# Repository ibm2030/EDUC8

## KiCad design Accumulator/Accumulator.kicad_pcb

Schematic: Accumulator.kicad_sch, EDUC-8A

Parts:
C1, C2, C3, C4: 47nF; C_Rect_L11.0mm_W2.8mm_P10.00mm_MKT
H1, H2: Card_handle
J1, J2: 16-way-pcb-edge-Educ-8-connectors; PCB_16pin
R1: 820; R_Axial_DIN0207_L6.3mm_D2.5mm_P10.16mm_Horizontal
R2, R3, R4: 2K2; R_Axial_DIN0207_L6.3mm_D2.5mm_P10.16mm_Horizontal
U1, U3: 74LS95; DIP-14_W7.62mm_LongPads
U2, U4: 74LS05; DIP-14_W7.62mm_LongPads
U5, U10: 74LS01; DIP-14_W7.62mm_LongPads
U6: 74LS04; DIP-14_W7.62mm_LongPads
U7, U9: 7400
U8: 74LS10

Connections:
+5V: C1.1, C2.1, C3.1, C4.1, J1.2, J1.3, R1.2, R2.1, R3.1, R4.1, U1.14 (VCC), U2.14 (VCC), U3.14 (VCC), U4.14 (VCC), U5.14 (VCC), U6.14 (VCC), U7.14 (VCC), U8.14 (VCC), U9.14 (VCC), U10.14 (VCC)
A-BUS: J1.4, U5.4, U6.9
AC0: J1.11, J2.9, U1.4 (P2), U1.10 (Q3), U2.9, U9.2, U9.13, U10.3, U10.5, U10.12
AC1: J2.10, U1.3 (P1), U1.11 (Q2), U2.11
AC2: J2.11, U1.2 (P0), U1.12 (Q1), U2.13
AC3: J2.12, U1.13 (Q0), U2.1, U3.5 (P3)
AC4: J2.13, U1.1 (Ds), U3.4 (P2), U3.10 (Q3), U4.9
AC5: J2.14, U3.3 (P1), U3.11 (Q2), U4.11
AC6: J2.15, U3.2 (P0), U3.12 (Q1), U4.13
AC7: J2.16, U1.5 (P3), U2.5, U3.13 (Q0)
AC=0: J1.15, R1.1, U2.2, U2.6, U2.8, U2.10, U2.12, U4.8, U4.10, U4.12
B-BUS: J1.5, U5.1, U10.1, U10.4
C-BUS: J1.6, U10.13
CPA: U1.9 (Cp1.Rshift), U3.9 (Cp1.Rshift), U7.8
D-BUS: J1.7, U9.1
GND: C1.2, C2.2, C3.2, C4.2, H1.1, H2.1, J1.1, J1.16, U1.7 (GND), U2.7 (GND), U3.7 (GND), U4.7 (GND), U5.7 (GND), U6.7 (GND), U7.7 (GND), U8.7 (GND), U9.7 (GND), U10.7 (GND)
MCP: J1.9, U7.1
unnamed: R2.2, U5.13, U9.9
unnamed: R3.2, U10.6, U10.10
unnamed: R4.2, U4.2, U5.3
unnamed: U3.1 (Ds), U6.8
unnamed: U5.2, U9.11
unnamed: U5.5, U9.6
unnamed: U5.6, U6.2
unnamed: U5.11, U7.6
unnamed: U6.12, U8.3
unnamed: U7.2, U8.12
unnamed: U7.4, U7.5, U8.8
unnamed: U7.3, U7.9, U7.10
unnamed: U8.2, U9.8
unnamed: U9.3, U9.4, U9.5
unnamed: U7.11, U10.2
unnamed: U8.6, U10.8, U10.9
unnamed: U6.4, U10.11
RAL: U1.6 (Mode), U3.6 (Mode), U6.5, U6.10
T1: J1.13, U1.8 (Cp2.Lshift), U3.8 (Cp2.Lshift)
T2-9: J1.12, U9.10
~AND: J2.1, U6.1, U8.10
~CLA: J2.8, U5.12, U8.5, U9.12
~CMA: J2.7, U4.1, U8.4
~DCA: J2.3, U6.3, U8.9
~IAC: J2.5, U6.13
~IOT_Shift: J1.10, U8.11
~RAL: J2.6, U6.11
~RAR: J2.4, U7.12
~T2-9(TAD+IAC+CMA): J1.14, U8.13
~T13.RAR: J1.8, U8.1
~TAD: J2.2, U7.13

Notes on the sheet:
7410
7495
Hex inverter OC
U6C
7405
Part No
Description
Quad NAND OC
U4B
820R
U5C
1/4 watt resistor
1. C-BUS not terminated on Accumulator board. Bus terminaing located in lower left quadrant of E8/C
2K2
Polyester capacitor
shift register
2. Tie floating input gates to GND.
E8-A Accumulator
7404
Hex inverter
Triple 3 input NAND
0.47uF
U4C
RAR
U2B
7400
Refdes
4. J1 and J2 are card edge etched onto PCB
Gates not used
Quad NAND
7401
7401
U10
5. Numbers in blue refer to original EDUC-8 Card edge connection
3. Add 0.1uf decoupling capacitor to the undersideof PCB between +5v and GND

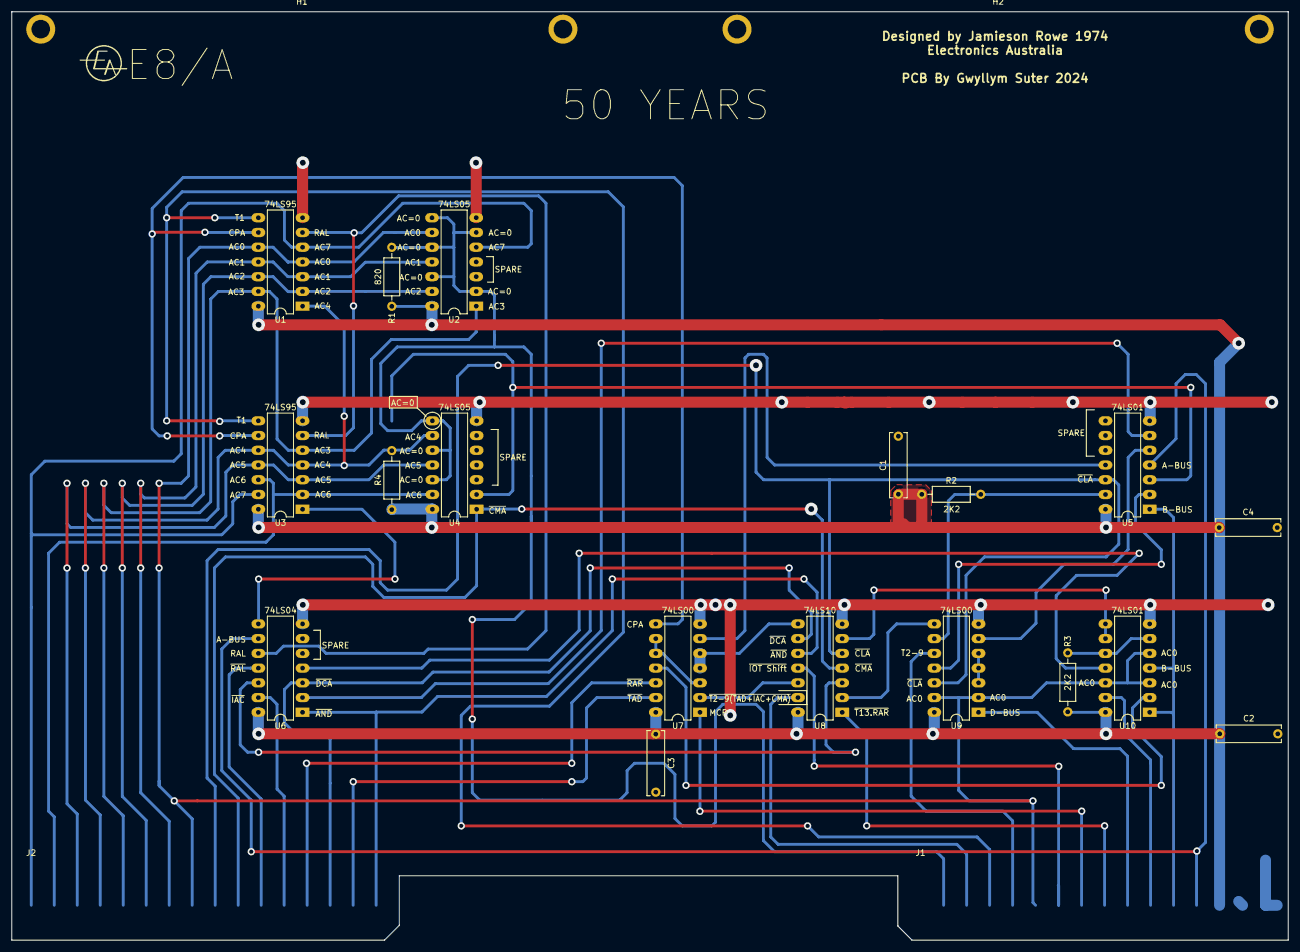
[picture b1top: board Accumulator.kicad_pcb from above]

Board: 2 copper layers, 220.0 x 160.0 mm, 22 parts (0 on the bottom side), 48 nets.

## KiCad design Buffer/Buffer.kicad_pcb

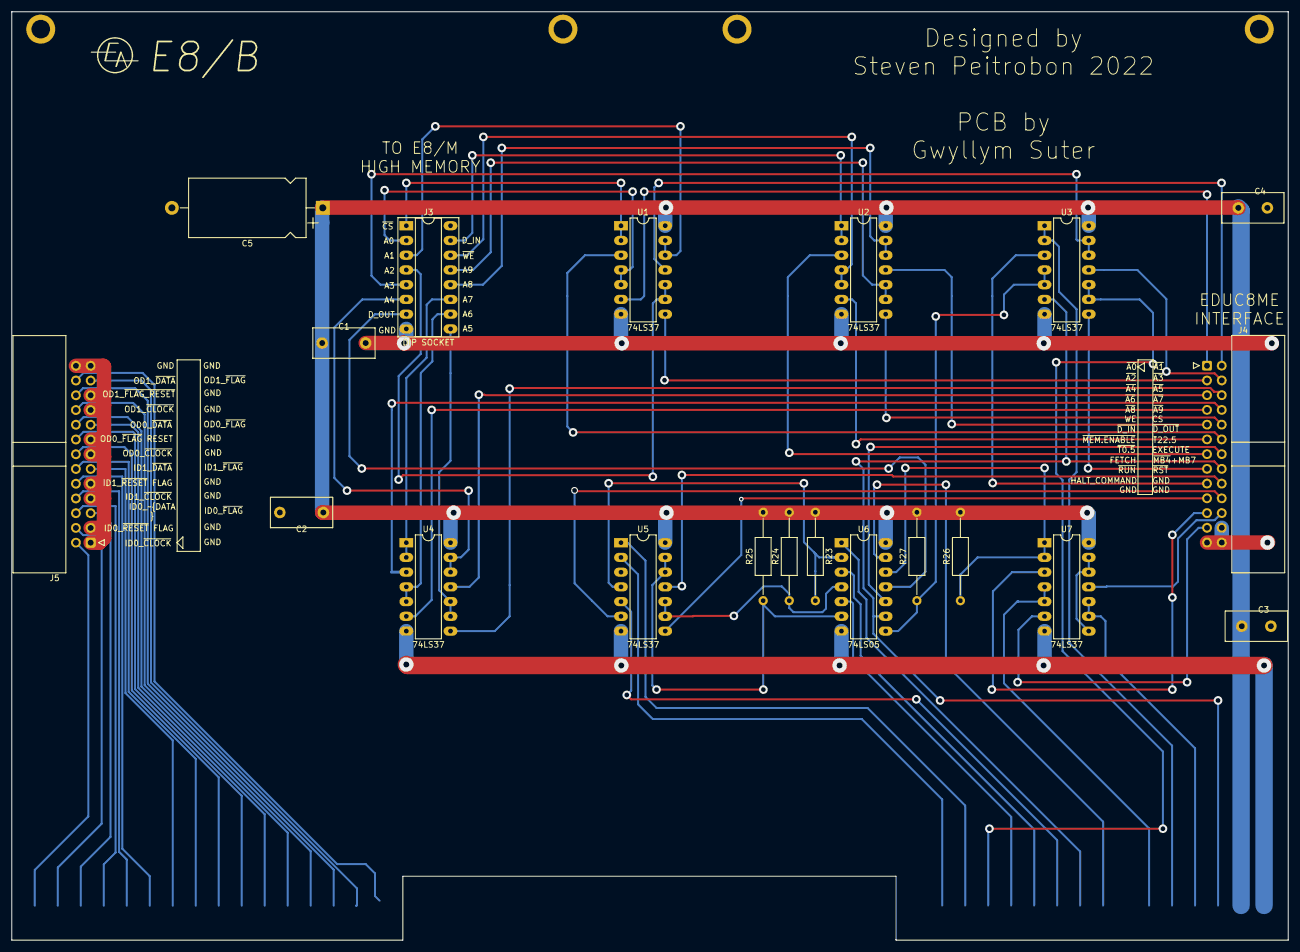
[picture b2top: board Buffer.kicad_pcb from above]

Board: 2 copper layers, 220.0 x 160.0 mm, 24 parts (0 on the bottom side), 72 nets.

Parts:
C1, C2: 470nF; C_Disc_D10.5mm_W5.0mm_P7.50mm
C3, C4: 470nF; C_Disc_D10.5mm_W5.0mm_P5.00mm
C5: 100uF; CP_Axial_L20.0mm_D10.0mm_P26.00mm_Horizontal
H1, H2: Card_handle
J1, J2: 16-way-pcb-edge-Educ-8-connectors; PCB_16pin
J3: DIP SOCKET; DIP-16_W7.62mm_Socket_LongPads
J4, J5: Conn_02x13_Odd_Even; IDC-Header_2x13_P2.54mm_Horizontal
R23, R24, R25, R26, R27: R_Small; R_Axial_DIN0207_L6.3mm_D2.5mm_P15.24mm_Horizontal
U1, U2, U3, U4, U5, U7: 74LS37; DIP-14_W7.62mm_LongPads
U6: 74LS05; DIP-14_W7.62mm_LongPads

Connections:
*EXECUTE: J4.18, U5.11
*FETCH: J4.19, U5.8
+5V: C1.1, C2.1, C3.1, C4.1, C5.1, J1.2, R23.1, R24.2, R25.2, R26.2, R27.2, U1.14, U2.14, U3.14, U4.14, U5.14, U6.14, U7.14
A0: J3.2, U1.4, U1.5
A1: J3.3, U1.12, U1.13
A2: J3.4, U1.9, U1.10
A3: J3.5, U3.12, U3.13
A4: J3.6, U4.12, U4.13
A5: J3.9, U4.9, U4.10
A6: J3.10, U4.4, U4.5
A7: J3.11, U4.1, U4.2
A8: J3.12, U2.12, U2.13
A9: J3.13, U2.9, U2.10
CS: J4.12, U1.3
D_IN: J3.15, U2.1, U2.2
D_OUT: J3.7, U6.11
EXECUTE: J1.12, U6.5
FETCH: J1.11, U6.3
GND: C1.2, C2.2, C3.2, C4.2, C5.2, H1.1, H2.1, J1.1, J1.16, J3.8, J4.24, J4.25, J4.26, J5.1, J5.3, J5.7, J5.9, J5.13, J5.15, J5.19, J5.21, J5.25, J5.26, U1.7, U2.7, U3.7, U4.7, U5.7, U6.7, U7.7
HALT_COMMAND: J1.6, U7.4, U7.5
ID0_~CLOCK: J2.16, J5.2
ID0_~DATA: J2.13, J5.6
ID0_~FLAG: J2.14, J5.5
ID0_~RESET_FLAG: J2.15, J5.4
ID1_~CLOCK: J2.12, J5.8
ID1_~DATA: J2.9, J5.12
ID1_~FLAG: J2.10, J5.11
ID1_~RESET_FLAG: J2.11, J5.10
JMP: J1.15, U5.2
JMS: J1.14, U5.1
MB4: J1.9, U6.1
MB7: J1.10, U5.5
MEM.ENABLE: J1.13, U3.9, U3.10
unnamed: R23.2, U5.4, U6.2
unnamed: R24.1, U5.9, U5.10, U6.4
unnamed: R25.1, U5.12, U5.13, U6.6
unnamed: R26.1, U6.12, U7.1, U7.2
unnamed: R27.1, U3.4, U3.5, U6.8
unnamed: U7.8, U7.12, U7.13
OD0_~CLOCK: J2.8, J5.14
OD0_~DATA: J2.5, J5.18
OD0_~FLAG: J2.6, J5.17
OD0_~RESET_FLAG: J2.7, J5.16
OD1_~CLOCK: J2.4, J5.20
OD1_~DATA: J2.1, J5.24
OD1_~FLAG: J2.2, J5.23
OD1_~RESET_FLAG: J2.3, J5.22
T0.5: J1.5, U3.1, U3.2
T22.5: J1.3, J4.16, U3.6, U6.9
WE: J4.11, U2.6
~A0: J4.1, U1.6
~A1: J4.2, U1.11
~A2: J4.3, U1.8
~A3: J4.4, U3.11
~A4: J4.5, U4.11
~A5: J4.6, U4.8
~A6: J4.7, U4.6
~A7: J4.8, U4.3
~A8: J4.9, U2.11
~A9: J4.10, U2.8
~CS: J3.1, U1.1, U1.2
~D_IN: J4.13, U2.3
~D_OUT: J4.14, U6.10
~HALT_COMMAND: J4.23, U7.6
~MB4+~MB7: J4.20, U5.6
~MEMORY_ENABLE: J4.15, U3.8
~RST: J1.4, U7.9, U7.10
~RST*: J4.22, U7.11
~RUN: J1.8, U6.13
~RUN*: J4.21, U7.3
~T0.5: J4.17, U3.3
~WE: J3.14, U2.4, U2.5

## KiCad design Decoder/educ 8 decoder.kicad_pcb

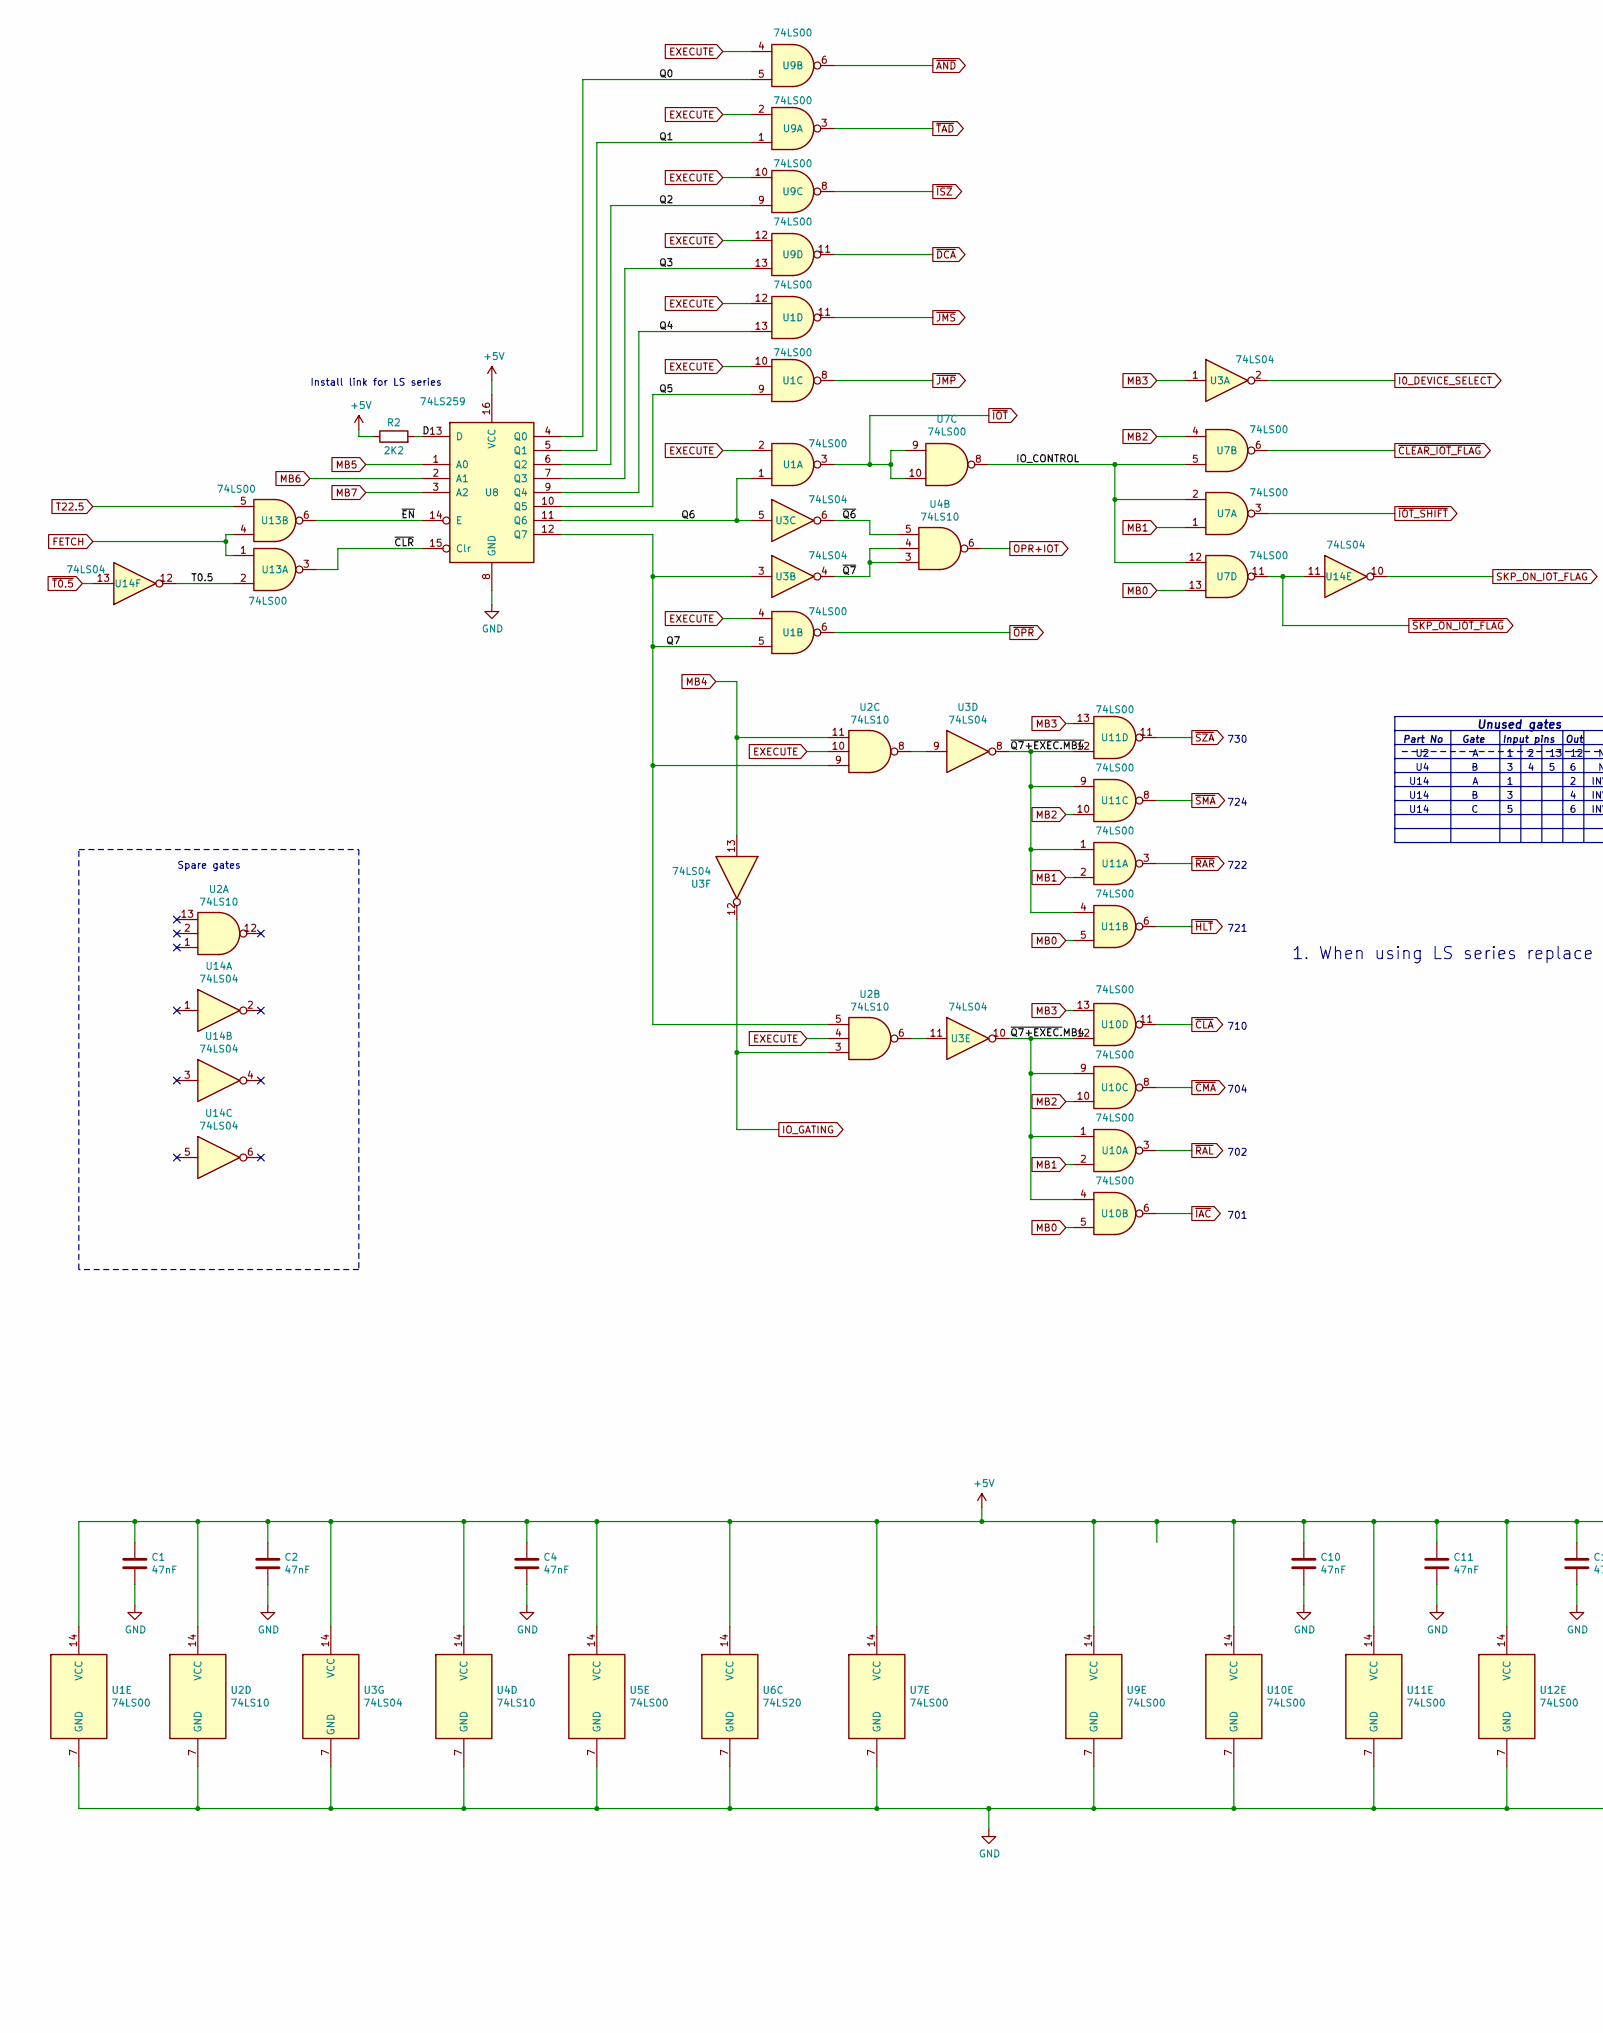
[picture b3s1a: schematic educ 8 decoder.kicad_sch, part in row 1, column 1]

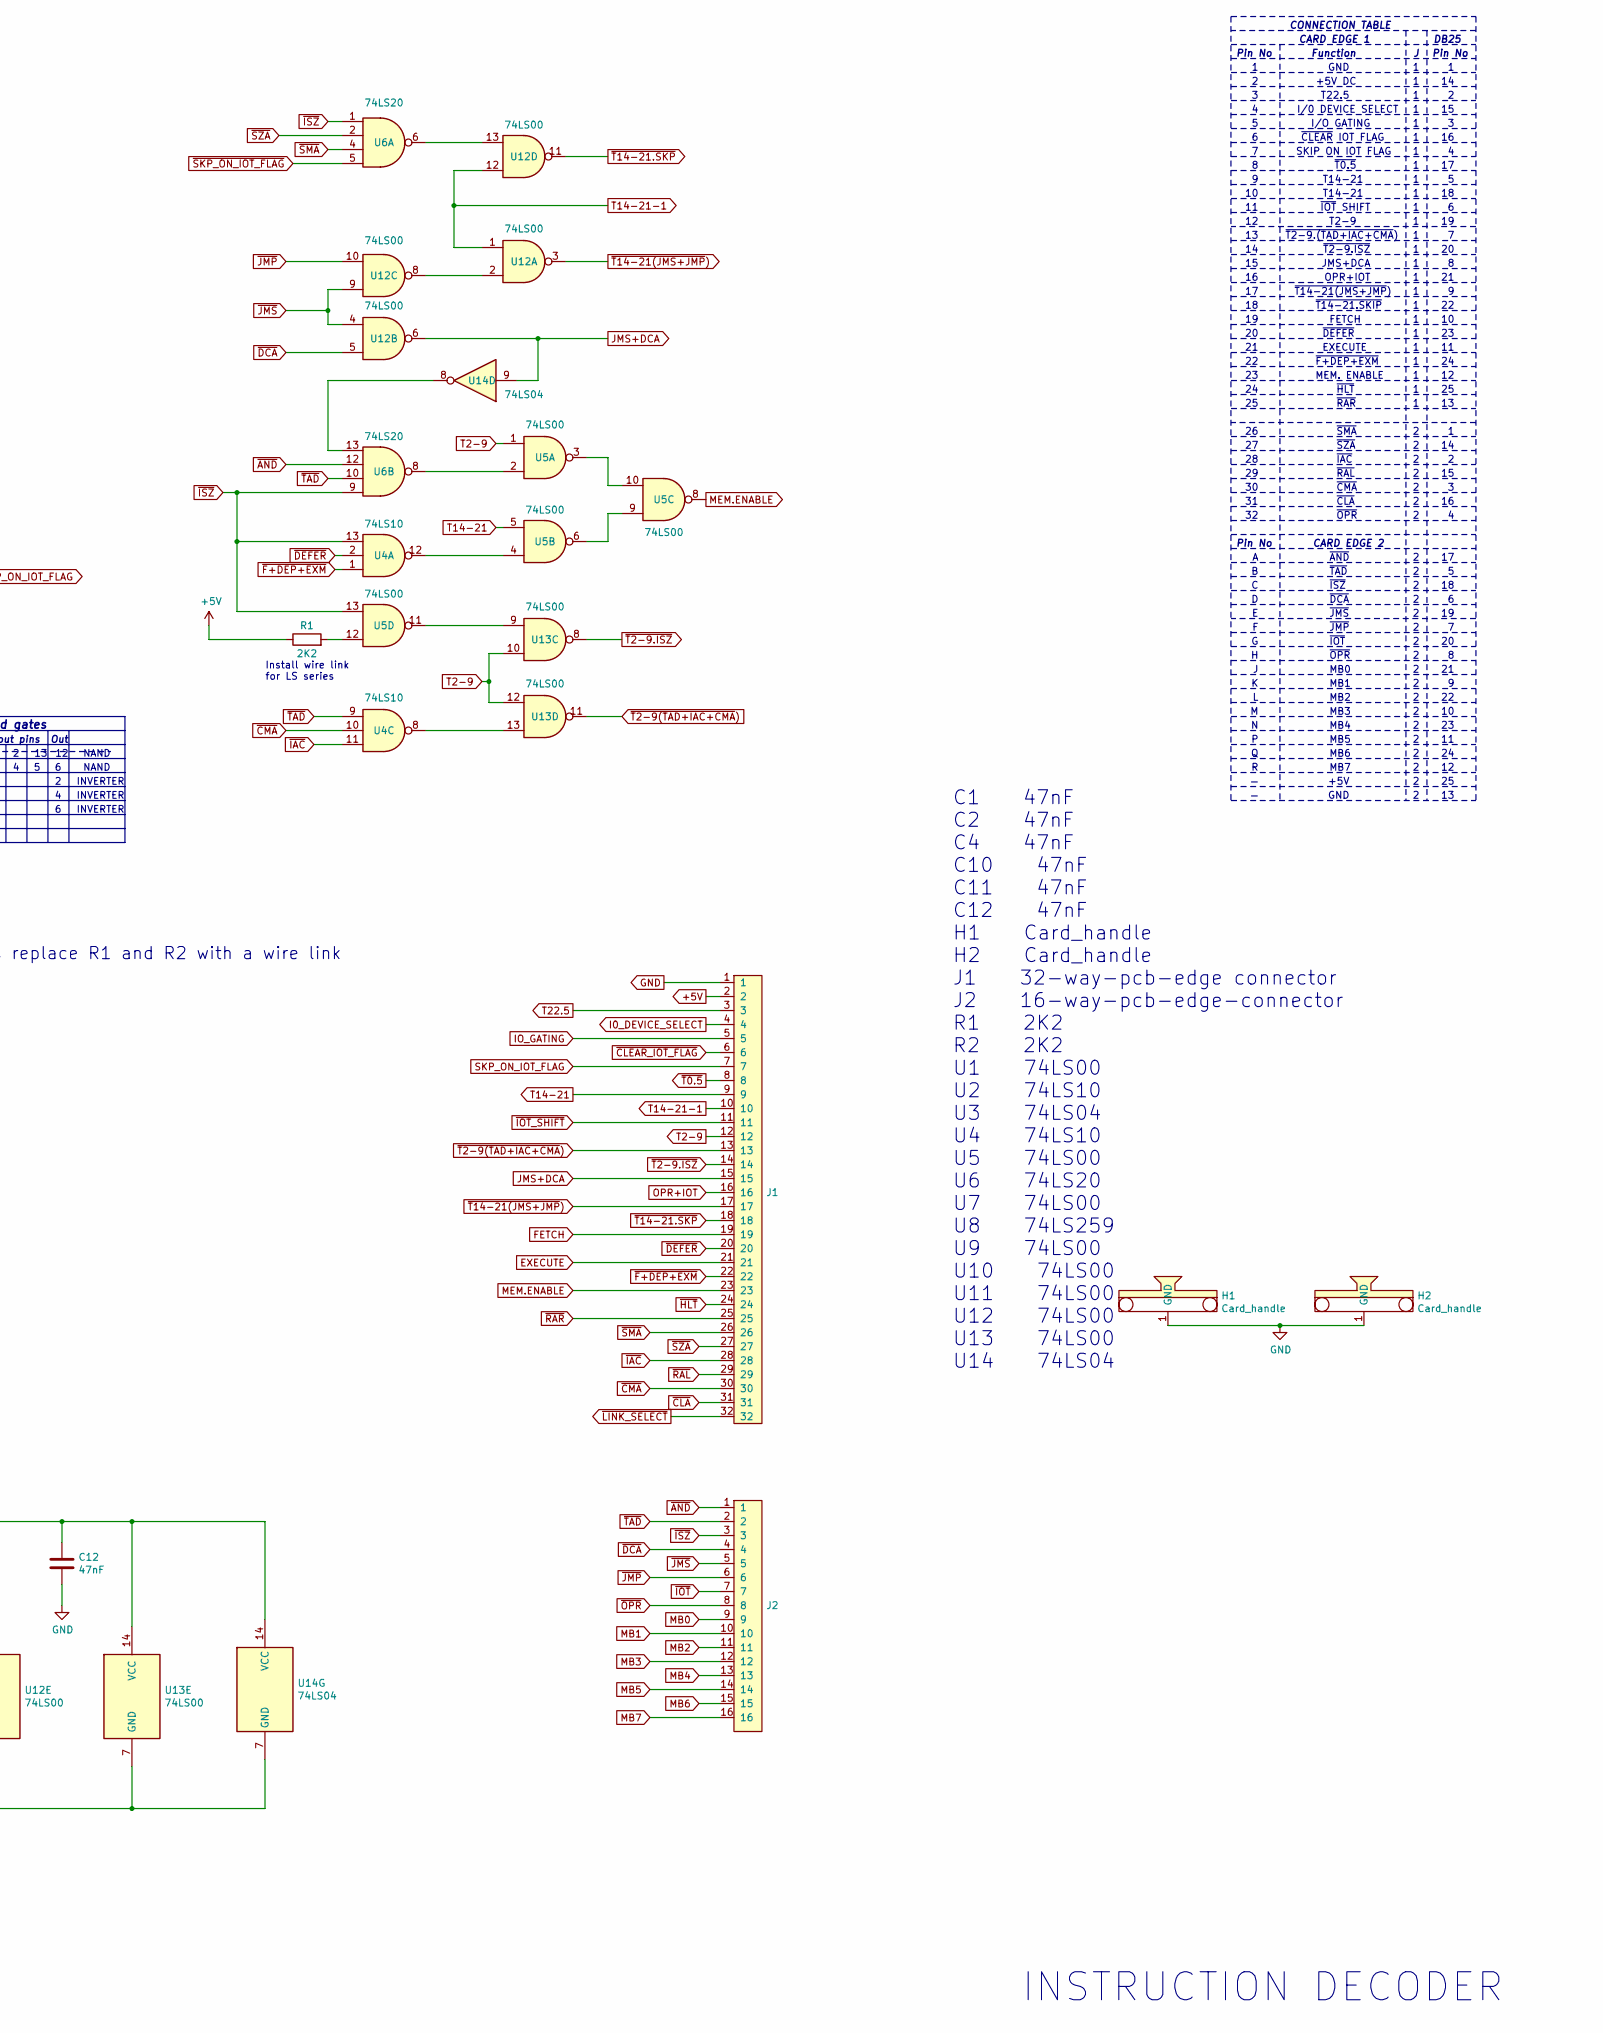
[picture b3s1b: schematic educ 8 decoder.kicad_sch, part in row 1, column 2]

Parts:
C1, C2, C4, C10, C11, C12: 47nF; C_Disc_D7.5mm_W2.5mm_P5.00mm
H1, H2: Card_handle
J1: 32-way-pcb-edge-Educ-8-connectors; PCB_32pin
J2: 16-way-pcb-edge-Educ-8-connectors; PCB_16pin
R1, R2: 2K2; R_Axial_DIN0414_L11.9mm_D4.5mm_P15.24mm_Horizontal
U1, U7, U9, U10, U11, U12: 74LS00; DIP-14_W7.62mm_LongPads
U2, U4: 74LS10; DIP-14_W7.62mm_LongPads
U3, U14: 74LS04; DIP-14_W7.62mm_LongPads
U5: 74LS00
U6: 74LS20; DIP-14_W7.62mm_LongPads
U8: 74LS259; DIP-16_W7.62mm_LongPads
U13: 74LS00; iot_shift

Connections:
+5V: C1.1, C2.1, C4.1, C10.1, C11.1, C12.1, J1.2, R1.1, R2.1, U1.14 (VCC), U2.14 (VCC), U3.14 (VCC), U4.14 (VCC), U5.14 (VCC), U6.14 (VCC), U7.14 (VCC), U8.16 (VCC), U9.14 (VCC), U10.14 (VCC), U11.14 (VCC), U12.14 (VCC), U13.14 (VCC), U14.14 (VCC)
/D: R2.2, U8.13 (D)
/IO_CONTROL: U7.2, U7.5, U7.8, U7.12
/Q0: U8.4 (Q0), U9.5
/Q1: U8.5 (Q1), U9.1
/Q2: U8.6 (Q2), U9.9
/Q3: U8.7 (Q3), U9.13
/Q4: U1.13, U8.9 (Q4)
/Q5: U1.9, U8.10 (Q5)
/Q6: U1.1, U3.5, U8.11 (Q6)
/Q7: U1.5, U2.5, U2.9, U3.3, U8.12 (Q7)
/~CLR: U8.15 (Clr), U13.3
/~EN: U8.14 (E), U13.6
/~Q6: U3.6, U4.5
/~Q7+EXEC.MB4: U3.8, U11.1, U11.4, U11.9, U11.12
/~Q7+EXEC.MB4: U3.10, U10.1, U10.4, U10.9, U10.12
/~Q7: U3.4, U4.3, U4.4
EXECUTE: J1.21, U1.2, U1.4, U1.10, U1.12, U2.4, U2.10, U9.2, U9.4, U9.10, U9.12
GND: C1.2, C2.2, C4.2, C10.2, C11.2, C12.2, H1.1 (GND), H2.1 (GND), J1.1, U1.7 (GND), U2.7 (GND), U3.7 (GND), U4.7 (GND), U5.7 (GND), U6.7 (GND), U7.7 (GND), U8.8 (GND), U9.7 (GND), U10.7 (GND), U11.7 (GND), U12.7 (GND), U13.7 (GND), U14.7 (GND)
I0_DEVICE_SELECT: J1.4, U3.2
IO_GATING: J1.5, U2.3, U3.12
JMS+DCA: J1.15, U12.6, U14.9
MB0: J2.9, U7.13, U10.5, U11.5
MB1: J2.10, U7.1, U10.2, U11.2
MB2: J2.11, U7.4, U10.10, U11.10
MB3: J2.12, U3.1, U10.13, U11.13
MB4: J2.13, U2.11, U3.13
MB5: J2.14, U8.1 (A0)
MB6: J2.15, U8.2 (A1)
MB7: J2.16, U8.3 (A2)
MEM.ENABLE: J1.23, U5.8
unnamed: R1.2, U5.12
unnamed: U2.6, U3.11
unnamed: U2.8, U3.9
unnamed: U4.12, U5.4
unnamed: U5.2, U6.8
unnamed: U5.6, U5.9
unnamed: U5.3, U5.10
unnamed: U12.2, U12.8
unnamed: U6.6, U12.13
unnamed: U5.11, U13.9
unnamed: U4.8, U13.13
unnamed: U6.13, U14.8
OPR+IOT: J1.16, U4.6
SKP_ON_IOT_FLAG: J1.7, U14.10
T2-9: J1.12, U5.1, U13.10, U13.12
T14-21: J1.9, U5.5
T14-21-1: J1.10, U12.1, U12.12
~AND: J2.1, U6.12, U9.6
~CLA: J1.31, U10.11
~CLEAR_IOT_FLAG: J1.6, U7.6
~CMA: J1.30, U4.10, U10.8
~DCA: J2.4, U9.11, U12.5
~DEFER: J1.20, U4.2
~F+DEP+EXM: J1.22, U4.1
~HLT: J1.24, U11.6
~IAC: J1.28, U4.11, U10.6
~IOT_SHIFT: J1.11, U7.3
~IOT: J2.7, U1.3, U7.9, U7.10
~ISZ: J2.3, U4.13, U5.13, U6.1, U6.9, U9.8
~JMP: J2.6, U1.8, U12.10
~JMS: J2.5, U1.11, U12.4, U12.9
~OPR: J2.8, U1.6
~RAL: J1.29, U10.3
~RAR: J1.25, U11.3
~SKP_ON_IOT_FLAG: U6.5, U7.11, U14.11
~SMA: J1.26, U6.4, U11.8
~SZA: J1.27, U6.2, U11.11
~T0.5: J1.8, U14.13
~T2-9(TAD+IAC+CMA): J1.13, U13.11
~T2-9.ISZ: J1.14, U13.8
~T14-21(JMS+JMP): J1.17, U12.3
~T14-21.SKP: J1.18, U12.11
~TAD: J2.2, U4.9, U6.10, U9.3

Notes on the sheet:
Install wire link for LS series
~{CLA}
MB5
U14
704
~{T2-9.ISZ}
Spare gates
CONNECTION TABLE
~{CLEAR} IOT FLAG
INVERTER
I/O GATING
MB4
+5V
EXECUTE
T22.5
Pin No
NAND
Unused gates
Install link for LS series
~{IOT}
~{DEFER}
~{TAD}
~{ISZ}
1. When using LS series replace R1 and R2 with a wire link
MB2
Function
Input pins
T14-21
CARD EDGE 2
~{RAL}
~{OPR}
Gate
MB6
JMS+DCA
~{T14-21(JMS+JMP})
GND
~{SMA}
MB0
~{RAR}
CARD EDGE 1

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
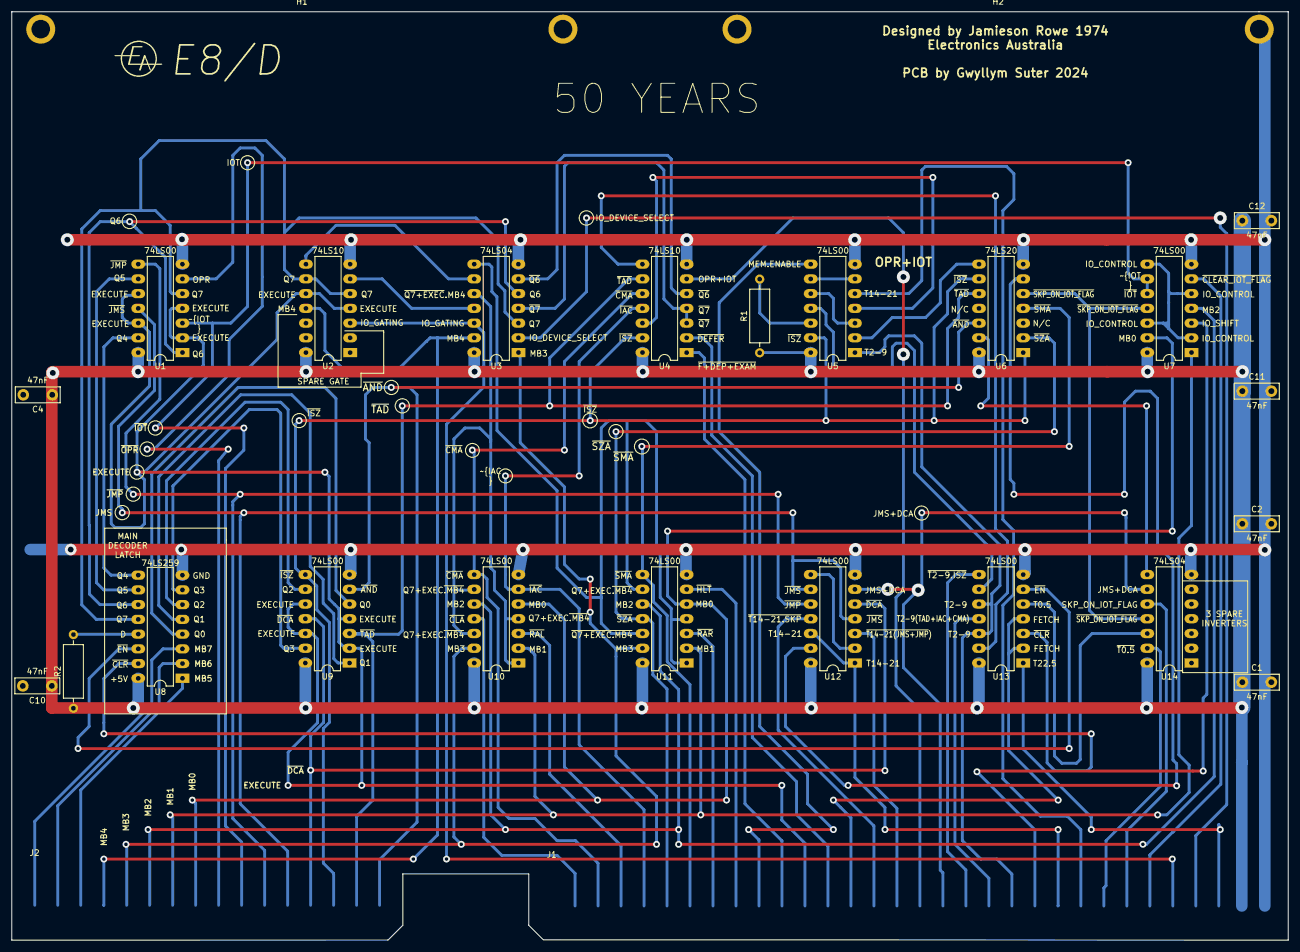
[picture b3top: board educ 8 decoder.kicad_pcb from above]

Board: 2 copper layers, 220.0 x 160.0 mm, 26 parts (0 on the bottom side), 77 nets.

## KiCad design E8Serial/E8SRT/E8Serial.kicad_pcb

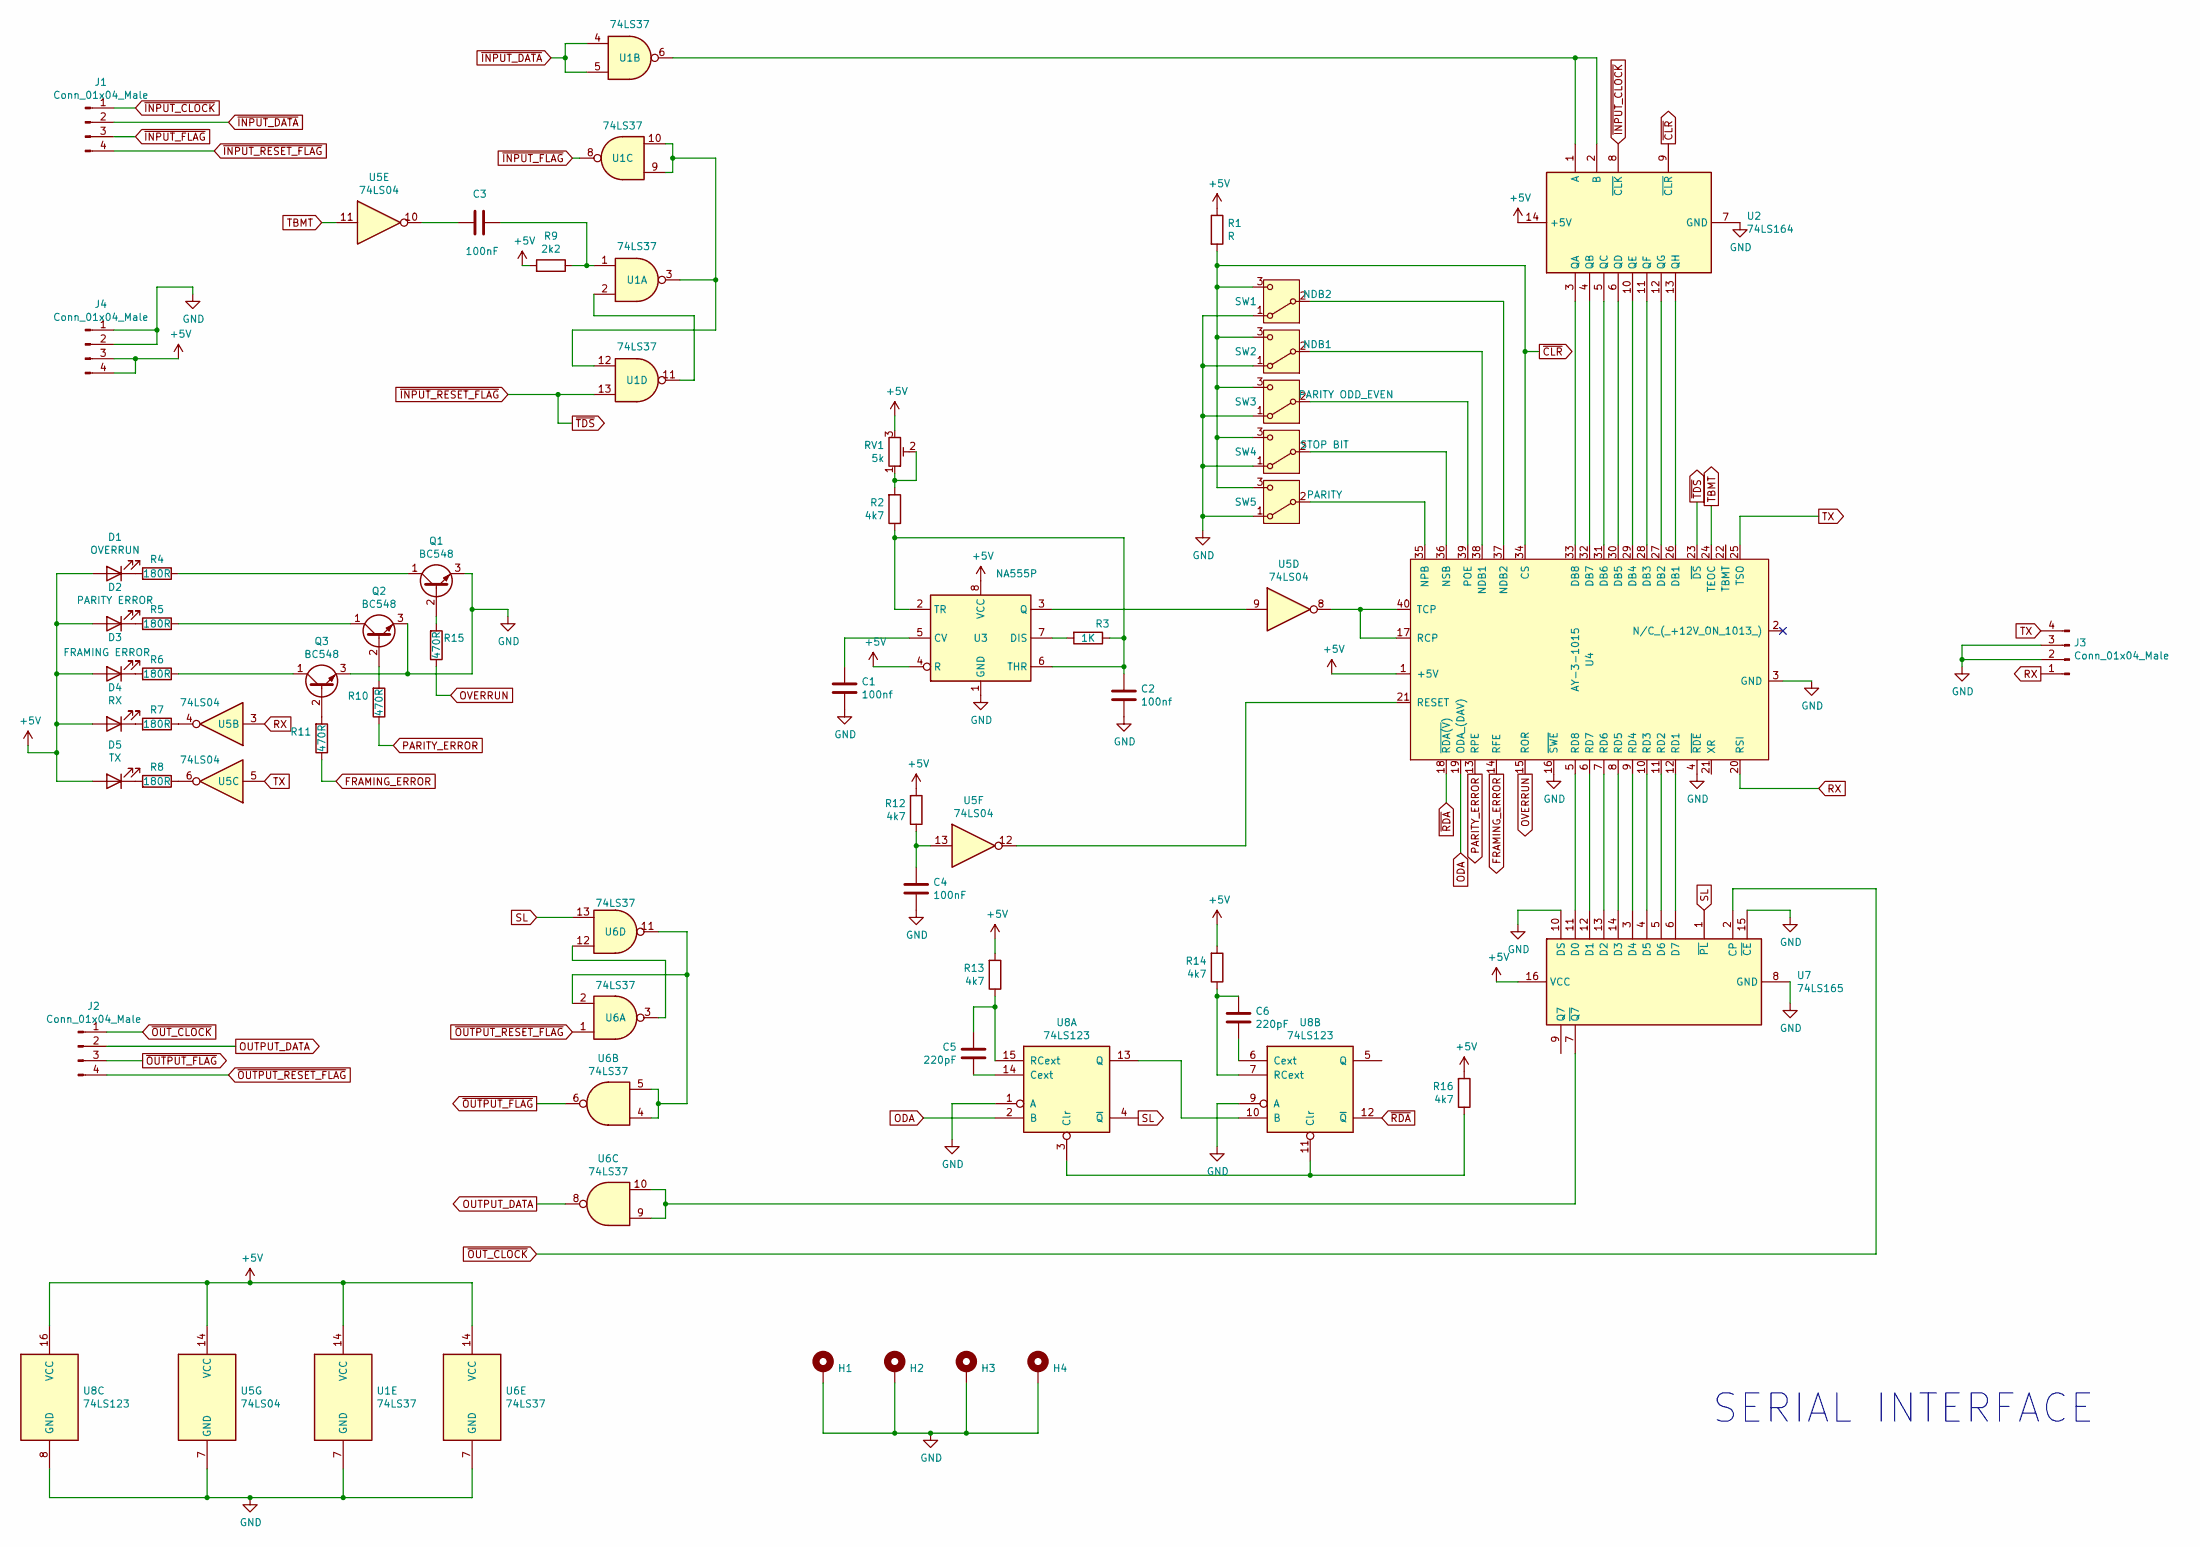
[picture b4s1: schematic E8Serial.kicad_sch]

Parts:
C1, C2: 100nf; C_Disc_D10.0mm_W2.5mm_P5.00mm
C3, C4: 100nF; C_Disc_D10.0mm_W2.5mm_P5.00mm
C5, C6: 220pF; C_Disc_D8.0mm_W2.5mm_P5.00mm
D1: OVERRUN; LED_D5.0mm_Horizontal_O3.81mm_Z9.0mm
D2: PARITY ERROR; LED_D5.0mm_Horizontal_O3.81mm_Z9.0mm
D3: FRAMING ERROR; LED_D5.0mm_Horizontal_O3.81mm_Z9.0mm
D4: RX; LED_D5.0mm_Horizontal_O3.81mm_Z9.0mm
D5: TX; LED_D5.0mm_Horizontal_O3.81mm_Z9.0mm
H1, H2, H3, H4: MountingHole_Pad; MountingHole_3.2mm_M3_Pad_Via
J1, J2, J3, J4: Conn_01x04_Male; PinHeader_1x04_P2.54mm_Vertical
Q1, Q2, Q3: BC548; TO-92_Inline_Wide
R1: R; R_Axial_DIN0207_L6.3mm_D2.5mm_P10.16mm_Horizontal
R2, R12, R13, R14, R16: 4k7; R_Axial_DIN0207_L6.3mm_D2.5mm_P10.16mm_Horizontal
R3: 1K; R_Axial_DIN0207_L6.3mm_D2.5mm_P10.16mm_Horizontal
R4, R5, R6, R7, R8: 180R; R_Axial_DIN0207_L6.3mm_D2.5mm_P10.16mm_Horizontal
R9: 2k2; R_Axial_DIN0207_L6.3mm_D2.5mm_P10.16mm_Horizontal
R10, R11, R15: 470R; R_Axial_DIN0207_L6.3mm_D2.5mm_P10.16mm_Horizontal
RV1: 5k; Potentiometer_Bourns_3006P_Horizontal
SW1: NDB2; S1320_SPDP_Toggle_switch_PCB_right_angle
SW2: NDB1; S1320_SPDP_Toggle_switch_PCB_right_angle
SW3: PARITY ODD_EVEN; S1320_SPDP_Toggle_switch_PCB_right_angle
SW4: STOP BIT; S1320_SPDP_Toggle_switch_PCB_right_angle
SW5: PARITY; S1320_SPDP_Toggle_switch_PCB_right_angle
U1, U6: 74LS37; DIP-14_W7.62mm
U2: 74LS164; DIP-14_W7.62mm
U3: NA555P; DIP-8_W7.62mm
U4: AY-3-1015; DIP-40_W15.24mm
U5: 74LS04; DIP-14_W7.62mm
U7: 74LS165; DIP-16_W7.62mm
U8: 74LS123; DIP-16_W7.62mm

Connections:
+5V: D1.2 (A), D2.2 (A), D3.2 (A), D4.2 (A), D5.2 (A), J4.3, J4.4, R1.1, R9.2, R12.2, R13.2, R14.2, R16.2, RV1.3, U1.14 (VCC), U2.14 (+5V), U3.4 (R), U3.8 (VCC), U4.1 (+5V), U5.14 (VCC), U6.14 (VCC), U7.16 (VCC), U8.16 (VCC)
FRAMING_ERROR: R11.1, U4.14 (RFE)
GND: C1.2, C2.2, C4.2, H1.1, H2.1, H3.1, H4.1, J3.2, J3.3, J4.1, J4.2, Q1.3 (E), Q2.3 (E), Q3.3 (E), SW1.1 (A), SW2.1 (A), SW3.1 (A), SW4.1 (A), SW5.1 (A), U1.7 (GND), U2.7 (GND), U3.1 (GND), U4.3 (GND), U4.4 (~RDE), U4.16 (~SWE), U5.7 (GND), U6.7 (GND), U7.8 (GND), U7.10 (DS), U7.15 (~CE), U8.1 (A), U8.8 (GND), U8.9 (A)
unnamed: C3.1, R9.1, U1.1
unnamed: C3.2, U5.10
unnamed: C4.1, R12.1, U5.13
unnamed: D1.1 (K), R4.2
unnamed: D2.1 (K), R5.2
unnamed: D3.1 (K), R6.2
unnamed: D4.1 (K), R7.2
unnamed: D5.1 (K), R8.2
unnamed: Q1.2 (B), R15.2
unnamed: Q1.1 (C), R4.1
unnamed: Q2.2 (B), R10.2
unnamed: Q2.1 (C), R5.1
unnamed: Q3.2 (B), R11.2
unnamed: Q3.1 (C), R6.1
unnamed: R2.2, RV1.1, RV1.2
unnamed: R7.1, U5.4
unnamed: R8.1, U5.6
unnamed: SW1.2 (B), U4.37 (NDB2)
unnamed: SW2.2 (B), U4.38 (NDB1)
unnamed: SW3.2 (B), U4.39 (POE)
unnamed: SW4.2 (B), U4.36 (NSB)
unnamed: SW5.2 (B), U4.35 (NPB)
unnamed: U1.3, U1.9, U1.10, U1.12
unnamed: U1.2, U1.11
unnamed: U1.6, U2.1 (A), U2.2 (B)
unnamed: U2.3 (QA), U4.33 (DB8)
unnamed: U2.4 (QB), U4.32 (DB7)
unnamed: U2.5 (QC), U4.31 (DB6)
unnamed: U2.6 (QD), U4.30 (DB5)
unnamed: U2.10 (QE), U4.29 (DB4)
unnamed: U2.11 (QF), U4.28 (DB3)
unnamed: U2.12 (QG), U4.27 (DB2)
unnamed: U2.13 (QH), U4.26 (DB1)
unnamed: C1.1, U3.5 (CV)
unnamed: R3.2, U3.7 (DIS)
unnamed: U3.3 (Q), U5.9
unnamed: C2.1, R2.1, R3.1, U3.2 (TR), U3.6 (THR)
unnamed: U4.17 (RCP), U4.40 (TCP), U5.8
unnamed: U4.12 (RD1), U7.6 (D7)
unnamed: U4.11 (RD2), U7.5 (D6)
unnamed: U4.10 (RD3), U7.4 (D5)
unnamed: U4.9 (RD4), U7.3 (D4)
unnamed: U4.8 (RD5), U7.14 (D3)
unnamed: U4.7 (RD6), U7.13 (D2)
unnamed: U4.6 (RD7), U7.12 (D1)
unnamed: U4.5 (RD8), U7.11 (D0)
unnamed: U4.21 (RESET), U5.12
unnamed: U6.2, U6.4, U6.5, U6.11
unnamed: U6.3, U6.12
unnamed: U6.9, U6.10, U7.7 (~Q7)
unnamed: C5.2, U8.14 (Cext)
unnamed: R16.1, U8.3 (Clr), U8.11 (Clr)
unnamed: U8.10 (B), U8.13 (Q)
unnamed: C5.1, R13.1, U8.15 (RCext)
unnamed: C6.2, U8.6 (Cext)
unnamed: C6.1, R14.1, U8.7 (RCext)
ODA: U4.19 (ODA_(DAV)), U8.2 (B)
OUTPUT_DATA: J2.2, U6.8
OVERRUN: R15.1, U4.15 (ROR)
PARITY_ERROR: R10.1, U4.13 (RPE)
RX: J3.1, U4.20 (RSI), U5.3
SL: U6.13, U7.1 (~PL), U8.4 (~Q)
TBMT: U4.24 (TEOC), U5.11
TX: J3.4, U4.25 (TSO), U5.5
~CLR: R1.2, SW1.3 (C), SW2.3 (C), SW3.3 (C), SW4.3 (C), SW5.3 (C), U2.9 (~CLR), U4.34 (CS)
~INPUT_CLOCK: J1.1, U2.8 (~CLK)
~INPUT_DATA: J1.2, U1.4, U1.5
~INPUT_FLAG: J1.3, U1.8
~INPUT_RESET_FLAG: J1.4, U1.13, U4.23 (~DS)
~OUTPUT_FLAG: J2.3, U6.6
~OUTPUT_RESET_FLAG: J2.4, U6.1
~OUT_CLOCK: J2.1, U7.2 (CP)
~RDA: U4.18 (~RDA(V)), U8.12 (~Q)

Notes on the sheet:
SERIAL INTERFACE
